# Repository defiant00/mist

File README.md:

# Mist

Mist is a one-handed symmetrical and columnar keyboard, with mirrored thumb keys providing 17 usable keys for either hand. It is ideal for anyone needing to type with one hand, or those wanting a staggered one-handed macro pad that can be used with either hand.

The name comes from its primary design goals: **MI**rrored, **ST**aggered.

Mist exists because accessibility should be more accessible. Commercial one-handed keyboards can be prohibitively expensive, and there are few open source keyboards designed specifically for one-handed use. Through this and the [purple firmware/layout project](https://github.com/defiant00/purple) we hope to provide another option.

## Parts

* 1x PCB
* 1x Adafruit Feather (recommended: [RP2040](https://www.adafruit.com/product/4884))
* 19x Kailh Choc switches
* 19x Choc spacing 1u keycaps (recommended: MBK)
* Some stick on feet
* **Optional**
  * Extra PCB as a bottom plate
  * M2 standoffs and screws
  * Adafruit Featherwings (OLEDs, LEDs, etc.) or STEMMA QT accessories if your Feather supports them

## Assembly

1. Solder on the Feather and switches. You can slot the Feather if you prefer.
2. **Optional** - Attach the extra PCB as a bottom plate using standoffs and screws at the five mounting points.
3. Keycaps!
4. Apply feet near the corners of the board.

## Release Notes

### 1.0 [2022-01-02]

* Initial version

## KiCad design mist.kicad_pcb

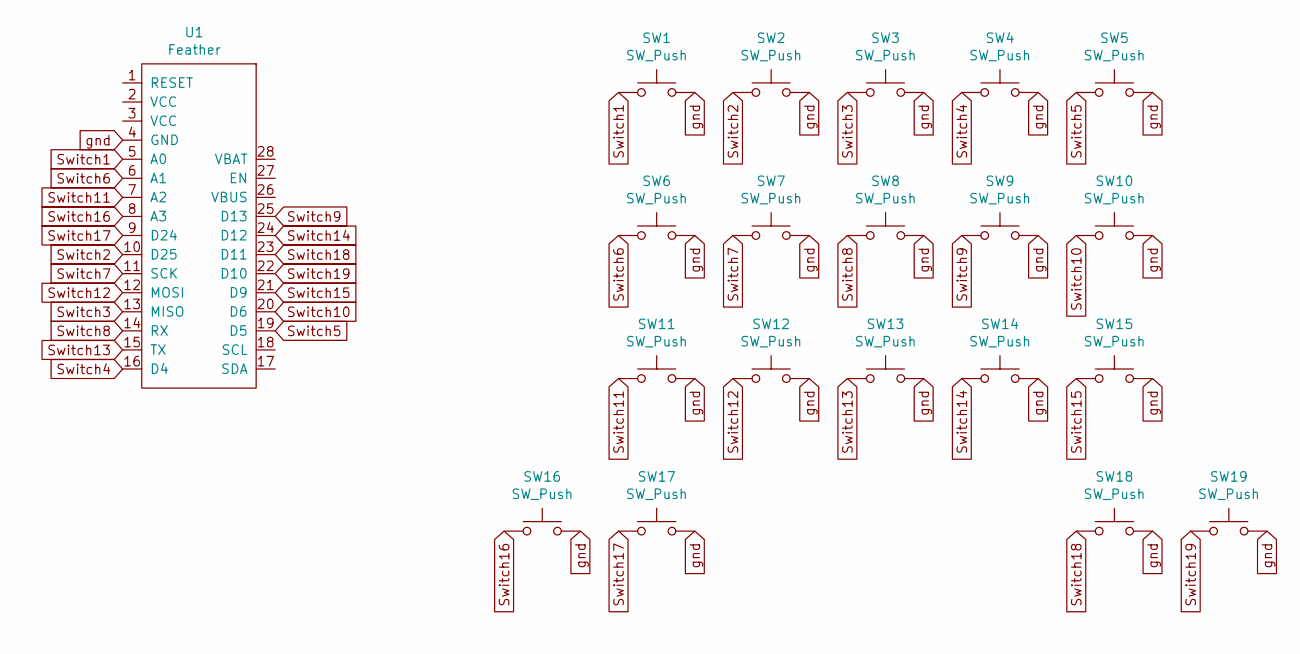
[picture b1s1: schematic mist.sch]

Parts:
SW1, SW2, SW3, SW4, SW5, SW6, SW7, SW8, SW9, SW10, SW11, SW12, SW13, SW14, SW15, SW16, SW17, SW18, SW19: SW_Push; Kailh-PG1350-1u-Clickhole-NoLED
U1: Feather; Adafruit_Feather

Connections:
Switch1: SW1.1, U1.5 (A0)
Switch2: SW2.1, U1.10 (D25)
Switch3: SW3.1, U1.13 (MISO)
Switch4: SW4.1, U1.16 (D4)
Switch5: SW5.1, U1.19 (D5)
Switch6: SW6.1, U1.6 (A1)
Switch7: SW7.1, U1.11 (SCK)
Switch8: SW8.1, U1.14 (RX)
Switch9: SW9.1, U1.25 (D13)
Switch10: SW10.1, U1.20 (D6)
Switch11: SW11.1, U1.7 (A2)
Switch12: SW12.1, U1.12 (MOSI)
Switch13: SW13.1, U1.15 (TX)
Switch14: SW14.1, U1.24 (D12)
Switch15: SW15.1, U1.21 (D9)
Switch16: SW16.1, U1.8 (A3)
Switch17: SW17.1, U1.9 (D24)
Switch18: SW18.1, U1.23 (D11)
Switch19: SW19.1, U1.22 (D10)
gnd: SW1.2, SW2.2, SW3.2, SW4.2, SW5.2, SW6.2, SW7.2, SW8.2, SW9.2, SW10.2, SW11.2, SW12.2, SW13.2, SW14.2, SW15.2, SW16.2, SW17.2, SW18.2, SW19.2, U1.4 (GND)

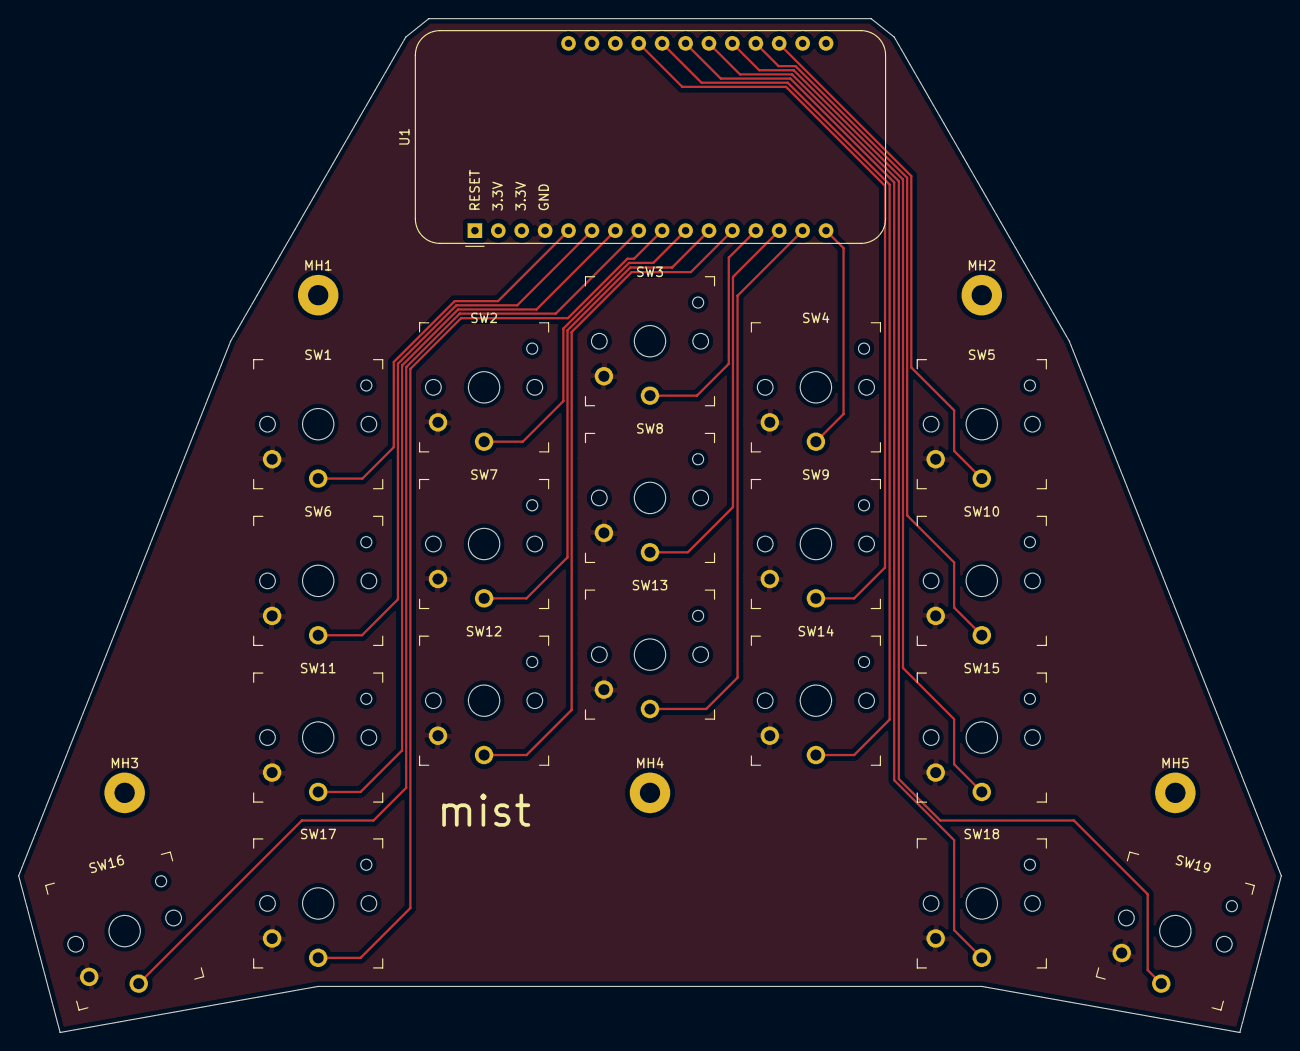
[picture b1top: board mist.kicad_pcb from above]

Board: 2 copper layers, 137.0 x 110.0 mm, 25 parts (0 on the bottom side), 20 nets.

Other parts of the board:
MH1, MH2, MH3, MH4, MH5: MountingHole_2.2mm_M2_Pad

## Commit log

2022-01-02 initial version
2022-01-03 added clickhole and gerbers
2022-01-15 removed untested warning
2022-01-22 added parts and assembly
2022-01-22 added image
2022-01-22 added image to readme
